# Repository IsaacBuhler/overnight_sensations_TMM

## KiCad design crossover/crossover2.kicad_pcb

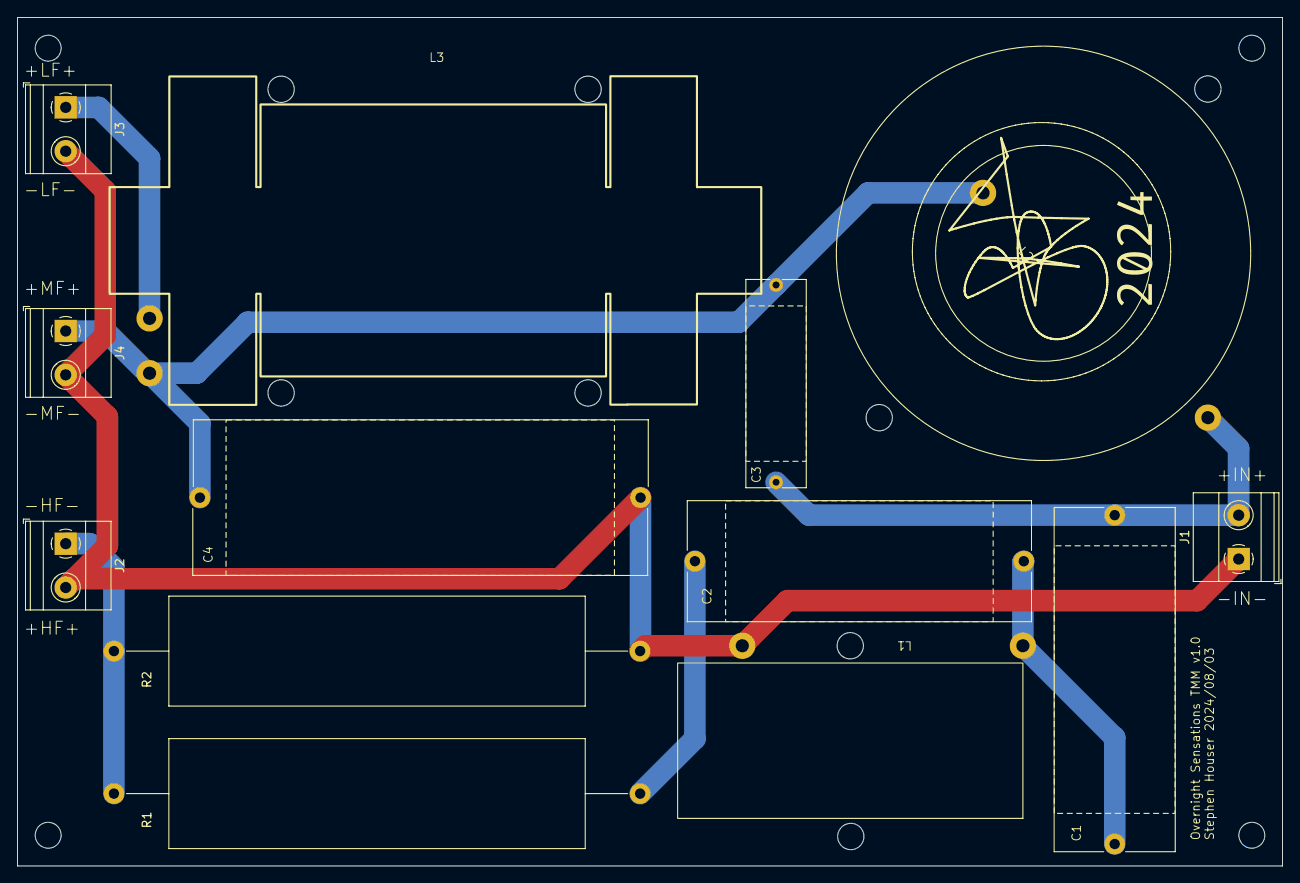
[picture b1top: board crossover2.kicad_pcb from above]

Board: 2 copper layers, 146.6 x 98.3 mm, 13 parts (0 on the bottom side), 7 nets.

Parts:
C1: 2.2uF; C_Audio_31x14
C2: 2.7uF; C_Audio_31x14
C3: 0.22uF; C_Audio_18x07
C4: 6.8uF; C_Audio_45x18
J1: In; TerminalBlock_Phoenix_MKDS-1,5-2-5.08_1x02_P5.08mm_Horizont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
J2: High; TerminalBlock_Phoenix_MKDS-1,5-2-5.08_1x02_P5.08mm_Horizont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
J3: Low; TerminalBlock_Phoenix_MKDS-1,5-2-5.08_1x02_P5.08mm_Horizont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
J4: Mid; TerminalBlock_Phoenix_MKDS-1,5-2-5.08_1x02_P5.08mm_Horizont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
L1: 0.30mH; L_Audio_D40_W18_Vertical
L2: 1.5mH; L_Audio_D48_W16_Horizontal
L3: 3.5mH; L_Audio_61x38_Iron
R1: 5.1; R_Axial_Power_L48.0mm_W12.5mm_P60.96mm
R2: 4.7; R_Axial_Power_L48.0mm_W12.5mm_P60.96mm

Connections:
HF+: C4.2, J1.1, J2.2, J3.2, J4.2, L1.2, R2.2
HF-: J2.1, R1.1, R2.1
IN+: C1.2, C3.2, J1.2, L2.2
LOW+: J3.1, L3.1
MID+: C3.1, C4.1, J4.1, L2.1, L3.2
unnamed: C1.1, C2.2, L1.1
unnamed: C2.1, R1.2
